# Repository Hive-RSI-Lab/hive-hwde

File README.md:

# hive-pcb-flow

The pcb-flow module: KiCad hardware design for the Hive, in the Hive org like the other modules. It began as ihsan-sa/pcb-flow's Claude Code skill and is its own now ([where it came from](docs/upstream.md)).

An agent designs a PCB from a written brief: research, architecture, parts, schematic, placement, routing, then the checks (ERC, DRC, the verify suite, JLCPCB DFM on the exported Gerbers), ending in a fab package. The person signs off between stages. Ordering and paying are always the person's.

**Where to file issues:** https://github.com/Hive-RSI-Lab/hive-hwde/issues, for a bug or for something that doesn't work on your machine (an Arm computer, another OS): say what you ran and what you saw. An agent in a Hive can draft the issue for you with `hive-report upstream draft`; you read it and press Send.

- [`docs/README.md`](docs/README.md): how an agent uses it in the Hive; [`docs/playbook.md`](docs/playbook.md): the phases, gates and fix loop
- `agents/`: the role prompts the playbook spawns; `scripts/`: the checks and tools; `reference/`: their tables, recipes, checklists and knowledge records
- `tests/`: unit tests for the scripts (`test_env_lookups.py`: the lookups for the Hive's shared tools folder), and `tests/workarounds/`, the probes
- `bin/pcb-flow`: runs the scripts in a Hive sandbox with the Hive's KiCad 10 and freerouting (`pcb-flow check` first)
- The first board made with it: [boards/hwde-led-test/](boards/hwde-led-test/)
- [docs/errata-corpus.md](docs/errata-corpus.md): public boards whose rev B fixed a rev A defect, and which of those defects pcb-flow's checks catch on rev A (`bin/pcb-flow errata_corpus fetch|run|table`)
- [docs/research/](docs/research/README.md): current research turned into checks: `bin/pcb-flow papers` scans the topics in `reference/research/watch.yaml`, reads legitimate open copies (the rest go on [the person's list](docs/research/paywalled.md)), and gives each claim pcb-flow's own verdict, with the test that reached it; only reproduced claims become [guidelines](docs/research/guidelines.md)
- [docs/route-quality.md](docs/route-quality.md): a layout judged as good, not only legal: `route_quality` scores each net class against its shortest 45-degree routes, `route_improve` re-routes the worst nets in rounds and stops when a round stops gaining

## Test and score

- **Test**, `bin/pcb-flow test`, run on every change: upstream's unit tests
  for the skill's scripts (in `tests/`, from ihsan-sa/pcb-flow, about 2,400 of
  them) and the workaround probes. It leaves out tests marked `smoke` (a
  live KiCad run) or `net` (the internet), and points `HWDE_BOARDS_ROOT` at
  an empty dir, so tests that want a real board skip. Upstream tests that
  fail here for a cause a brief already owns are expected failures, listed
  with that brief in `tests/conftest.py`; one that starts passing shows as
  XPASS, and its line comes out. `tests/test_workarounds.py` runs every
  probe in `tests/workarounds/` and fails when
  [docs/workarounds.md](docs/workarounds.md) doesn't match them: a cause
  that stands with no row, or a row whose cause is fixed. It also leaves
  out the tests listed as `slow` in `tests/conftest.py` (`SLOW`: the live
  toolchain, whole fixture boards through bench or the gates, intake of a
  whole project); `bin/pcb-flow test-slow` runs those, so run it too on a change
  to the checks, bench, intake or `check_env`. `bin/pcb-flow test-em` runs the long
  full-wave solves test-slow leaves out (`EM` in `tests/conftest.py`, 80 min
  against test-slow's 17 on a machine at load 45), so run it on a change to `scripts/lib/em*`
  or `scripts/lib/solvers.py`. A test past its limit (15 min, 45 in `em`) fails
  by name. `bin/pcb-flow test-smoke` runs the
  `smoke` tests, whole flows on a live KiCad; CI runs them on every PR and
  daily (`.github/workflows/smoke.yml`), and a failed daily run opens an issue. The test keeps its scratch
  files on `/dev/shm` when it has room and nothing in it fsyncs
  (`HWDE_NO_FSYNC`), because on a loaded disk the suite's file writes, not
  its CPU, set its time; it prints its time and its slowest 15 tests at
  the end. A few minutes; pytest arguments pass through
  (`bin/pcb-flow test tests/test_fab.py -x`).
- **Boards**, `bin/pcb-flow check-all`, not the per-change test: copies every
  board under `boards/` to a scratch dir and re-runs its gate steps there
  through `bin/pcb-flow`: `erc`, `drc_routed`, `verify`, `fab` (gerbers, drill,
  BOM and CPL from `fab_export` and `bom_cpl`) and `dfm`. A board runs each
  gate its `state.json` records as passed, and `fab` once it has a package
  in `fab/`. Any step that fails fails it, and it runs the probes too. Its
  time grows with every board, so run it on a change to the gates, the
  shims in `bin/pcb-flow` or a board, and before a release. Both need
  `/hive/tools`'s KiCad and the Hive's uv; on a fresh HOME they build the
  venv first. Inside a Hive turn both, and the scripts that run a whole
  board, the router or a sim (`route_auto`, `route_critical`,
  `place_anneal`, `gate`, `verify_all`, `bench`, `render`, `sim_run`,
  `sim_solve`, `fab_export`), run under `hive agent heavy`: they wait (at most 10
  minutes) while the machine is strained and other turns run one. A command
  already inside one (check-all's gates, a test that runs `bin/pcb-flow`), or a
  Hive without that op yet, runs bare (`tests/test_heavy.py`).
- **Score**, `bin/pcb-flow score`, higher is better: what this checkout's
  gates get wrong on boards held fixed. The hi-fi receiver's lite-main, core and ultra-front,
  pinned in `pinned/` at one hifi-receiver-2 commit, and hwde-led-test go
  through erc, drc_routed, verify and dfm with `bin/pcb-flow`'s shims off. Each board's
  ledger (`pinned/known/<board>.json`) judges its findings: one held real
  is the board's defect and costs nothing; one held false, one not judged
  yet, a known real one no gate reports any more, and each board-local
  script that stands in for pcb-flow is a charge, and the score is minus the
  charges. A fix in pcb-flow that clears a false finding on those boards raises
  it with nothing written by hand; a sharper check's new real findings go
  into the ledger in the same change. A pinned board changes only through `bin/pcb-flow pin`. The whole
  definition is [docs/score.md](docs/score.md). About ten minutes or more,
  under `hive agent heavy`. A looser check finds less, so the score also
  runs pcb-flow's planted faults (`bin/strength.py`: the gate criteria, every
  verify check's mutant in `tests/golden/`, dfm at JLC's floors), and each
  one a check lets through charges 100.

MIT, like upstream; see NOTICE for what that doesn't cover.

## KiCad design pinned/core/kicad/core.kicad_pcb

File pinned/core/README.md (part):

# core: the Plus/Ultra main board

The main board of hifi-receiver-2's **Plus** and **Ultra** tiers
([docs/product.md](../../docs/product.md)). It is a USB-C-powered
streaming amplifier on one 4-layer board, 154.4 x 113 mm (120 x 100 until the
banana sockets; see below):

- **Input:** 28 V USB PD EPR at up to 140 W.
- **Streaming:** ESP32 with Wi-Fi, Bluetooth and Ethernet.
- **Mains DAC:** Sabre ES9018K2M.
- **Subwoofers:** a separate sub DAC for two sub outputs.
- **Line in:** RCA, with a zero-latency "DJ direct" path.
- **Amp:** two TPA3220 class-D amps (the pad-down TPA3221): 2 x 77 W into 4 ohm peak, no heatsink. Plus plays L on zone A and R on zone B; Ultra drives two pairs.
- **Ultra population options:** a second amp (zone B), an optical input
  and the FFC to the `ultra-front` display board.

It was designed with the hive-hwde module (KiCad 10, JLCPCB) on 2026-10-28,
from schematic through routed layout to a JLC fab package. **Nothing has
been ordered. Ordering is the person's.**

## Status (2026-10-29)

All hwde gates pass on the routed board after the first-spin review ECO, with hive-hwde at c23e27e:

| Gate | Result |
|---|---|
| `erc` | 0 errors, 0 warnings |
| `place` | pass |
| `drc_routed` | 0 errors, 0 warnings, parity clean |
| `verify` | pass, 1 waiver (`reports/verify-waivers.json`: the ESP32 module's 3V3 decoupling loop) |
| `dfm` | pass on the exported Gerbers |

The fab package is in `fab/`:

- **Gerbers:** `core_gerbers.zip`.
- **Plus build:** `BOM.csv` (88 lines, every one with an LCSC number), `CPL.csv` (298 placed parts, 14 of them on the bottom: see `fab/ORDERING.md`), `BOM-full.csv` and `prebuy.csv`, which lists the Extended parts.
- **Ultra build:** `fab/ultra/` holds `BOM.csv` and `CPL.csv` (302 placed parts) for the same Gerbers.

Board facts:

- **Size:** 4 layers, 154.4 x 113 mm overall, 1.6 mm. The right-hand 34.4 mm
  is a wing along the rear only (y < 150 in KiCad); the front right stays
  notched so the ESP32's antenna is still at the board edge.
- **Stackup:** 4 layers, 1.6 mm, 1 oz outer and 1 oz inner. JLC04161H-1080B
  comes only with 0.5 oz inner, so leave Specify Stackup at no requirement
  on the quote page: JLC then builds a 0.203 mm 7628 prepreg and a 1.03 mm
  core, and a named 1 oz layup adds $51.20. No net here is impedance
  controlled. Order it with
  epoxy filled and capped vias (`fab/ORDERING.md`), and inner copper 1 oz, not JLC's 0.5 oz default: the In2 VBUS/PVDD planes carry
  the full 5 A on their own (`power_trunk.py`).
- **Vias:** 0.7/0.3 mm, plus a few 0.45/0.2 mm GND taps.
- **Mounting:** 4 x M3 plated holes.
- **Holes:** JLC's 0.5 mm hole-to-hole spacing is held everywhere.

hwde's own estimate for 10 boards with assembly is $278, $27.84 each. That
excludes the parts, and it is a lower bound: the PCB line has the
oversize-area bug that hive-hwde issue #12 fixes. JLC's cart is the real quote.

## What's on it

The full block list, the ESP32 GPIO map, the I/O expander map, the FFC
pinout and the power tree are in
[architecture/blocks.md](architecture/blocks.md). In short:

| Block | Parts |
|---|---|
| Power in | GCT USB4085-GF-A through-hole USB-C (48 V/5 A, 240 W), CH224Q PD sink (asks for 28 V; ESP32 can read it or change it over I2C), SMBJ30A TVS, 10 mΩ shunt + INA186 current sense |
| PVDD switch | AO4485 P-FET, on only when firmware sets PVDD_EN **and** the CH224Q's PG says the contract is good; ~60 ms soft start (0.47 A, 9.8 W peak); gross-overvoltage cut-off |
| Rails | SY8303 VBUS to 5.1 V; SY8089 5 V to 3.3 V; LP5907 3.3 V analog; ferrite-fed +5VA and +3V3E |
| Processor | ESP32-WROVER-E-N8R8; CH340B USB-serial on the same USB-C (auto-reset, flashing from a laptop) |
| Ethernet | LAN8720A + HR911105A magjack, gated 50 MHz RMII clock |
| Mains DAC | ES9018K2M at 49.152 MHz MCLK, OPA1678 differential-to-single-ended stage |
| Sub DAC | PCM5102A to a stacked dual RCA (SUB1, SUB2) |
| Line in | stacked dual RCA, ES7243E ADC, TS5A23157 DAC/DJ-direct selector |
| Self-measurement | zone A's A_SPK_L+/R+ through 150k/10k, 470 pF, 1 uF onto a 1.65 V bias; TS5A23157 U20 picks RCA input (default) or the taps for the ADC; select from expander P17 through Q7 |
| Zone A amp | TPA3220 (24 dB, AD mode, 600 kHz; pad down, 15 vias into the GND planes), 10 µH / 10 A filters, 4 board-mounted 4 mm banana sockets |
| Zone B amp [Ultra] | the same, synchronised to zone A as a peripheral |
| Control | TCA9539 I/O expander (0x74, reset with the ESP32's EN); Plus front-edge knob, 2 buttons, IR receiver, status LED |
| Optical [Ultra] | PLR237 TOSLINK into the ES9018K2M's S/PDIF mux |
| Front board [Ultra] | 20-pin 0.5 mm FFC to `ultra-front` |

## Plus and Ultra from one board

| Parts | Plus | Ultra |
|---|---|---|
| zone B amp, its filters, bulk cap (U16, L5-L8, C3xx/R3xx) | fitted (plays R) | fitted |
| speaker sockets J20/J21 (zone A L), J26/J27 (zone B R) | fitted | fitted |
| speaker sockets J22/J23 (zone A R), J24/J25 (zone B L) | not fitted | fitted |
| TOSLINK U19, FB3, C126 | not fitted | fitted |
| FFC J3, R402/R403 | not fitted | fitted |
| knob SW1, buttons SW2/SW3, IR U18 (+R400/C400) | fitted | not fitted |

`fab/BOM.csv`/`CPL.csv` are the **Plus** build. `fab/ultra/BOM.csv` and
`CPL.csv` are the **Ultra** build of the same Gerbers.

## Banana sockets (2026-11-01, issues #117, #124)

The speaker outputs are eight 4 mm banana sockets in one row along the rear
edge, 11 mm apart. From the left in KiCad (from behind the box it reads
right to left): J20 A L+, J21 A L-, J22 A R+, J23 A R-, J24 B L+, J25 B L-,
J26 B R+, J27 B R-. Red is +. Plus plays L on zone A and R on zone B
(`HIFI_SPLIT`), so it fits J20/J21 and J26/J27; Ultra fits all eight.

A socket reaches 21.4 mm into the board and its nose stands 2.65 mm past the
edge, so the board grew. The rear edge moved 13 mm back, and a 34.4 mm wing
on the right took the RCA jacks J4/J5 and the TOSLINK U19. They moved with
D7/D8, FB3 and C126 and the copper between them as one block. The mounting
holes H1/H2 went to the new rear corners (H2 later moved south along the east edge to (185.45, 127.4), to make room for the jacks' side ears: `kicad/gen/rca_ear_eco.py`). How it was done, from
`boards/core`, KiCad's python as `python3.11`:

1. `kicad/gen/blocks_amp.py`: the sockets replace the terminals. Then
   `hwde lib_pull --lcsc C7437321 C7437322`, `build.py` (only amp_a/amp_b
   kept), `parts/*.json` by hand, and the netlist.
2. `python3.11 kicad/gen/banana_eco.py kicad/core.kicad_pcb`: rips the old
   terminal copper and the stitch vias under the row, and cuts the speaker
   pours back to y 130. It moves the rear block and the holes, and redraws
   the outline and the planes.
3. `hwde board_update --placements kicad/gen/banana_placements.json`.
4. `python3.11 kicad/gen/banana_route.py kicad/core.kicad_pcb`: one
   staircase pour per speaker net from its old pour to its socket's pin 2.
   L-/R+ run on F.Cu and L+/R- on B.Cu, four per layer, with no crossings
   and no vias. The pours are 2 mm wide (3.7 A rms). Where a later band
   crosses below a socket, its pin 1 joins pin 2 by a 1 mm In2 link (J23,
   J24, J25).
5. `python3.11 kicad/gen/banana_snub.py kicad/core.kicad_pcb`: zone A R- and
   zone B L+'s snubbers reached their net through the old terminal pin. Each
   gets a via and a B.Cu stub into its pour.
6. `miniroute.py` relays SUB1/SUB2_OUT, LIN_L/LIN_R and OPT_SPDIF to the
   moved block. Each line still goes into its ESD clamp (D7/D8) before the
   jack. Stale stubs are ripped with `rip_at.py`, and
   `kicad/gen/banana_silk.py` drops the sockets' silk, as on Lite.
   `kicad/gen/banana_45.py` puts the route ends back on the 45-degree grid
   (hwde check_route_style).

Folded in from review 5: R5-PA-1 (C4 220 nF/50 V C344195, C8 4.7 uF/25 V
C1779: Q1's soft start stays in its SOA), the EP paste windows off the vias
for U9/U10/U13 (`kicad/gen/ep_paste.py`, hwde check_ep_paste), and the
footprints' LCSC fields from parts.json (`kicad/gen/lcsc_fields.py`, run by
`fab.sh`, R5-DAL-8).

## First-spin review (review-2, 2026-10-29)

Six independent reviewers (power, audio, digital/RF, thermal, DFM, parts
pin-to-pad) read this board from its KiCad files and the vendor datasheets:
[`docs/review-2/`](../../docs/review-2/). What changed on core because of it:

| Finding | Was | Now |
|---|---|---|
| DIGITAL-1/2, PARTS-4 (blocker): the TCA9555's pull-ups left PHY_RST (the 50 MHz oscillator into GPIO0, a boot strap), PVDD_EN and the amp/DAC resets mid-rail at power-up, and its outputs held through ESP32 resets | TCA9555, R45 100k | TCA9539 (no pull-ups; RESET = ESP_EN), R45 10k |
| POWER-1 (blocker): the 5 A path ran through 0.25 mm tracks and 1-3 vias | SMD USB4105, few vias | through-hole USB4085 (power pins solid into the In2 VBUS_IN plane), copper patches with 8 vias at R1's input, 10 from R1's output to Q1's source, 8 at Q1's drain; 3-4 per TPA3221 PVDD pin group |
| sim_inrush hard_reset (hwde 261029-050227): Q1's ~1.1 s gate RC outlasted tSrcRecover, so a hard-reset source charged PVDD's 940 uF through a still-on Q1 (14 A, Q1 426 C) | Q2 released, R4 alone pulls the gate | R404 + D5 + Q3's second NPN pull Q1's gate to VBUS in ~2 ms when Q2 lets go (PG lost, PVDD_EN low, OV trip), in hardware: 0.7 A, Q1 120 C in the sim |
| THERMAL-1/DFM-3 (blocker): TPA3221 is pad-up with no heatsink | none | U15/U16 swapped to the pin-identical pad-down TPA3220. Its EP is soldered to GND with 15 x 0.3 mm vias into In1/B.Cu, so nothing is fitted by hand. Plus fits both amps, one channel each (L on zone A, R on zone B), and the firmware governor holds the 60 s average to 19 W out, about 2.0 W per chip, in the vented box (9.6 W/ch into 4 ohm). See `docs/review-2/heatsink-options.md` and `firmware-requirements.md` C2/C3 |
| DFM-1 (blocker): RCA J4/J5 had no holes for the jack's snap-in legs | none | Lite's footprint: 2.0 x 3.0 leg holes, signal pins as slots that fit either reading of the drawing |
| PARTS-7/DFM-12 (blocker, Ultra): TOSLINK T8BK on a T10BK footprint | no post holes | the T8BK's two 1.70 mm post holes (NPTH, `kicad/gen/u19_posts.py`; until 2026-10-30 they were only in the library copy, not on the board) |
| DIGITAL-19 (major): copper under the Wi-Fi antenna on all 4 layers | GND/+3V3 pours, two tracks | `ANT_KEEPOUT` rule area x 148.9-154.64, y 189.6-213.5 on every layer; I2S_DIN and RMII_TXD1 rerouted |
| POWER-2 (major): Q1 turn-on outside its SOA | R4/R5 100k, C8 1 uF | 470k/470k, 2.2 uF/50 V |
| POWER-6 (major): no hardware PVDD cut when the PD contract is lost | Q2 source on GND | Q2 source on CH224Q PG (+ R20 10k pull-up), as on Lite |
| AUDIO-1 (major): OPA1678 at 48 mV of input headroom | R73/75/81/83 1.5k | 1.3k |
| AUDIO-2/3 (major): planned tap switch couldn't pass a node below 0 V or be driven from 3.3 V | (new) | biased tap nodes, Q7 level shift, default = RCA |
| DFM-4 (major): IR receiver looking at the lid | IRM-H638T | front-facing IRM-3638T at the front edge |
| PARTS-3/AUDIO-10, DIGITAL-5, AUDIO-5 (minor) | 50 MHz Y1, C47 100 nF, 1 uF ADC caps | 49.152 MHz, 1 uF, 4.7 uF |
| Stock | CH340C | CH340B |

Ultra's zone-B speaker taps (the bring-up ask) were left out: no control line
is left to choose a zone, and the extra switch crowded the ADC; zone B is
watched through FAULT/OTW and ISENSE. The ES9018K2M's GPIO2 was the first
choice for the tap select, but its pin can't be fanned out between GPIO1 and
DATA, so the select comes from expander P17 and the front board's LCD_CS is
held asserted by R57 (DIGITAL-16; firmware cs = -1).

The changes went in as an ECO on the routed board: `board_update`, the
reviewers' fixes in `kicad/gen/blocks*.py`, then the power patches (then
`via_array.py`, now hwde's `zone_patch`),
`ant_keepout.py`, `miniroute.py`, hwde's `route_auto` (its KRT fallback; Freerouting
stalled), `stitch_vias`, `island_vias.py`/`gnd_via_drops.py` and hand tracks
(`add_track.py`/`add_via.py`). IR_IN keeps a 25 mm hop on In1 (the GND plane)
under the front UI area, where nothing fast crosses it.

## Design decisions and why

These are the decisions that differ from, or add to, docs/product.md.

- **Current sense:** INA186 (40 V), not INA180. The INA180 stops at 26 V
  common mode, under the 28 V rail. The sense taps run through
  10 Ω + 100 nF, but they leave the input planes rather than R1's own pads, so U3 reads
  about 5.6% high (`check_kelvin`, waived in `reports/verify-waivers.json`). It errs on the
  safe side; set the gain at bring-up (`docs/firmware.md`).
- **DAC clock:** 49.152 MHz. With its internal 1.2 V DVDD the
  ES9018K2M is limited to 50 MHz; a 50 MHz part met it only at 0 ppm, so
  review-2 moved to 49.152 MHz (synchronous 1024 x 48 kHz). It covers
  24/96 PCM and 96 kHz S/PDIF.
- **Ethernet clock:** a 50 MHz oscillator drives both the PHY and ESP32
  GPIO0. ESP32 clock-out on GPIO0 is experimental in ESP-IDF. The
  oscillator's enable is the PHY reset line, so GPIO0 boots clean.
- **PVDD switch hold-off:** a gate-source capacitor (1 µF) plus a 15 V
  clamp. Without it, the P-FET turned on while VBUS stepped from 5 to 28 V
  and charged the bulk caps at source slew. A schematic review caught it.
- **Overvoltage cut-off:** a 33 V zener (trips about 32-36 V). It is a
  backstop against gross faults only: the TPA3220's absolute maximum is
  37 V, and a zener cannot trip accurately at 30 V without tripping at the
  legitimate 29.4 V EPR maximum.
- **Snubbers:** on the speaker side of the output filter, as in TI's
  figure 9-1. On the switching node a 1 nF snubber would dissipate 0.47 W
  in each resistor.
- **Speaker outputs:** eight board-mounted 4 mm banana sockets, Amass
  24.243 (red C7437321, black C7437322, 24 A), the part Lite uses. JLC fits
  them, so nothing is wired by hand (issues #117, #124). They replaced 2-way
  5 mm screw terminals, which needed posts in the box wired to them. See
  "Banana sockets" above.
- **Amp polarity:** the TPA3220 inverts. The DAC stage undoes it (U11's
  inputs are swapped), so OUTx_P is the speaker's + (blocks_amp.py).
- **DJ switch logic:** the expander's 3.3 V output can't drive the 5 V
  switch's logic (it needs VIH 3.5 V), so Q6 inverts it up to 5 V.
- **I2S:** one bit and frame clock for all three converters. The sub DAC
  takes its own data pin (I2S1 as slave), because the ESP32 has no pins to
  spare.
- **FFC pinout:** the ultra-front board's map. It needs SPI, I2C and an
  interrupt line, and the front board carries its own expander.
  J3 and ultra-front's J1 are the same socket at rotation 0, pin N on the
  same signal at both ends: the cable is 20-pin 0.5 mm **type B**, pin N to
  pin N (`docs/review-2/resolutions.json` parts:64).

## Rebuild and re-check

From this directory (`boards/core`), with `H="sh $HIVE_MODULES/hive-hwde/bin/hwde"`:

1. **Schematic:**
   `eval "$($H env)"; PYTHONPATH=$HWDE_SKILL/scripts:$HWDE_SKILL/scripts/lib $HWDE_PY kicad/gen/build.py`.
   The design is data in `kicad/gen/blocks*.py`.
2. **ERC:** `$H gate --gate erc kicad/core.kicad_sch --workspace $PWD`
3. **Board setup and placement:** `sh kicad/gen/rebuild_board.sh`. This
   runs board_init, rules_gen, the hand anchors in `kicad/gen/anchors.py`,
   then `kicad/gen/satellites.py` and the place gate.
4. **Routing:** `sh kicad/gen/route.sh` (planes, stitching, Freerouting).
5. **Routed checks and fab:** the `drc_routed`, `verify` and `dfm` gates,
   `fab_export`, and `bom_cpl` run once with `parts/parts.json` (Plus) and
   once with `parts/parts-ultra.json` into `fab/ultra` (Ultra).

The full GND stitching pass (272 vias) went on the routed board afterwards:
[`docs/boards/core-stitch.md`](../../docs/boards/core-stitch.md).

### C43 to the LAN8720A's VDD1A

C43 is the 100 nF on U9 pin 19. It sat 3.8 mm from the pin, but its copper reached the pin only
through 20.3 mm of +3V3E, out through J2.4 and back, so it did little for that pin. ETH_TXN
lies between the two tracks, so `kicad/gen/c43_eco.py` crosses under it on B.Cu with two 0.6/0.3 mm
vias and 1.8 mm of track. The walk is now 6.55 mm, inside hwde's 10 mm limit.

### The two U10 decoupling warnings, left as they are

hwde's `check_decoupling` warns twice on U10 (ES9018K2M). Both are warnings, not errors, and both are left on purpose (2026-11-04):

- **C53 to pin 16 (AVCC_R), 13.7 mm of +3V3A.** Pins 15 (AVCC_L), 16 (AVCC_R) and 17 (VCCA) are joined at the package, 0.5 mm apart.
  So pin 16 is also served by C50 (1 uF, 5.7 mm), C51 (100 nF, 6.1 mm), C54 (100 nF, 7.2 mm) and C52 (1 uF, 7.7 mm), all inside the 10 mm limit.
  C53 is a fifth cap on that group. Its long walk costs nothing the others don't already cover. Moving it would mean new copper beside the DAC outputs for no gain.
- **C55 to pin 18 (DVCC, +3V3), loop about 11.3 nH against a 10 nH limit.** That is 8.8 mm of rail, 3.0 mm of ground and three vias. DVCC is the digital supply that feeds the chip's own 1.2 V regulator, whose output pin 21 (DVDD) has C56 (4.7 uF).
  13 % over the limit moves the cap's self-resonance from about 5.0 to 4.7 MHz. That is not worth a copper change on a board about to be ordered.
  If bring-up shows DAC noise tied to the digital supply, the fix is a 100 nF 0402 placed beside pin 18 on the next spin.

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
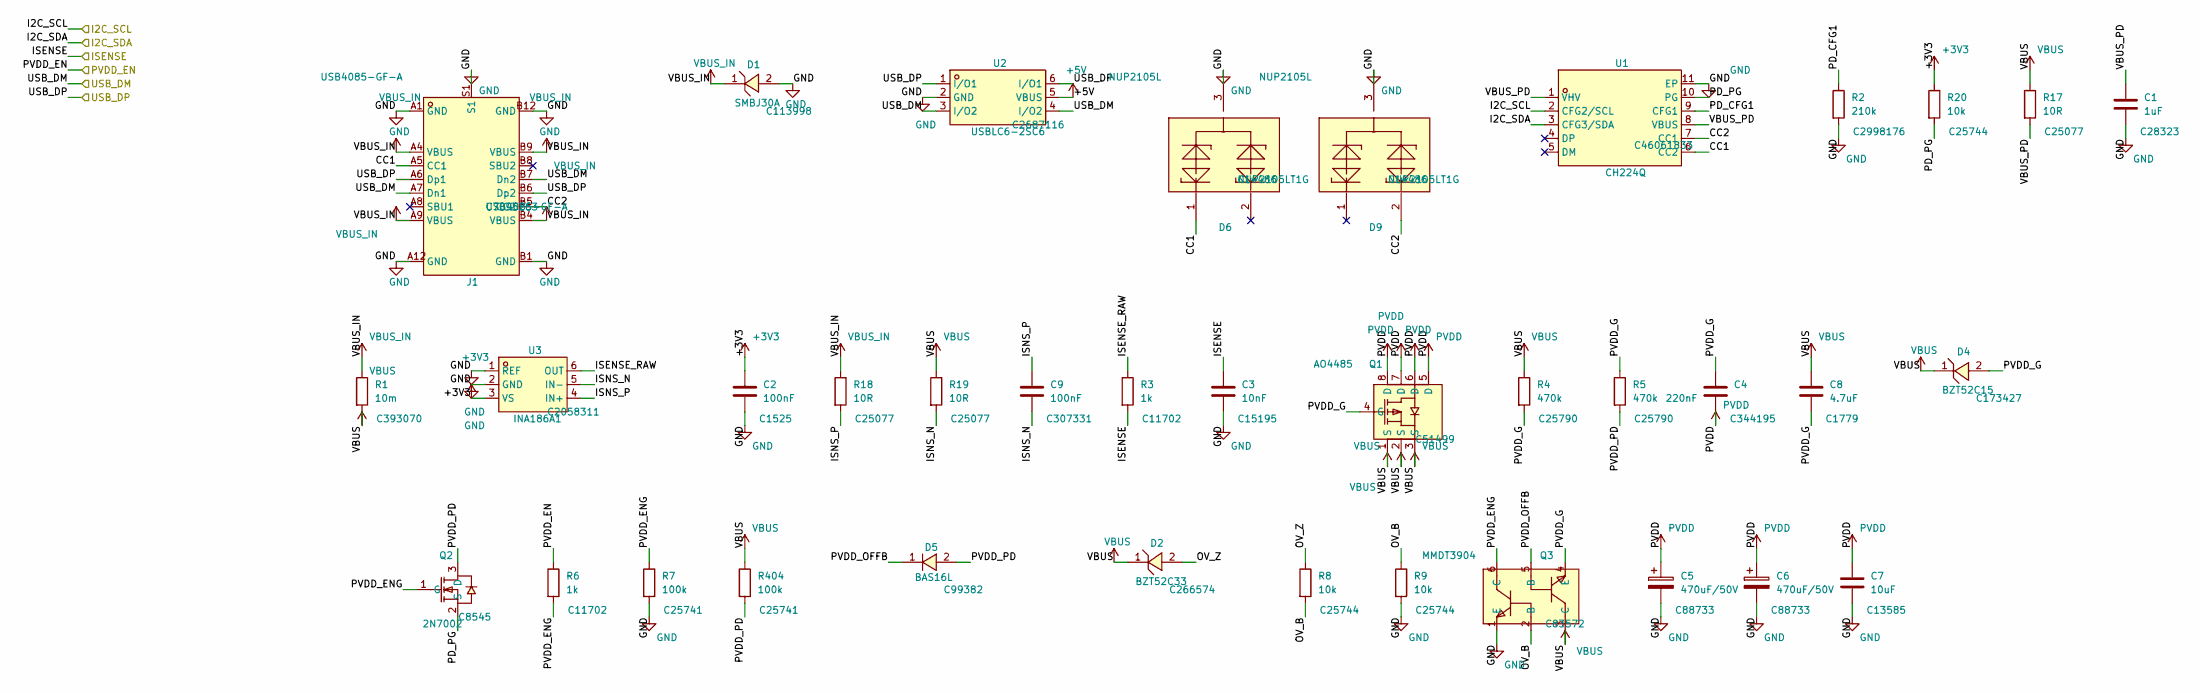
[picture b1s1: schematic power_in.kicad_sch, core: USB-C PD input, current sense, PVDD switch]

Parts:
C1: 1uF; C0805; LCSC C28323
C2: 100nF; C0402; LCSC C1525
C3: 10nF; C0402; LCSC C15195
C4: 220nF; C0603; LCSC C344195
C5, C6: 470uF/50V; CAP-TH_BD10.0-P5.00-D1.0-FD; LCSC C88733
C7: 10uF; C1206; LCSC C13585
C8: 4.7uF; C0805; LCSC C1779
C9: 100nF; C0402; LCSC C307331
D1: SMBJ30A; SMB_L4.6-W3.6-LS5.3-RD; LCSC C113998
D2: BZT52C33; SOD-123_L2.7-W1.6-LS3.7-RD; LCSC C266574
D4: BZT52C15; SOD-123_L2.7-W1.6-LS3.7-RD; LCSC C173427
D5: BAS16L; SOD-882_L1.0-W0.6-RD; LCSC C99382
D6, D9: NUP2105L; SOT-23-3_L2.9-W1.3-P1.90-LS2.4-BL-2; MPN NUP2105LT1G; LCSC C14486
J1: USB4085-GF-A; USC-C-SMD_USB4085-GF-A; MPN USB4085-GF-A; LCSC C7095263
Q1: AO4485; SOIC-8_L5.0-W4.0-P1.27-LS6.0-BL; LCSC C51499
Q2: 2N7002; SOT-23-3_L2.9-W1.3-P1.90-LS2.4-BR; LCSC C8545
Q3: MMDT3904; SOT-363_L2.0-W1.3-P0.65-LS2.1-TL; LCSC C83572
R1: 10m; R2512; LCSC C393070
R2: 210k; R0402; LCSC C2998176
R3, R6: 1k; R0402; LCSC C11702
R4, R5: 470k; R0402; LCSC C25790
R7, R404: 100k; R0402; LCSC C25741
R8, R9, R20: 10k; R0402; LCSC C25744
R17, R18, R19: 10R; R0402; LCSC C25077
U1: CH224Q; DFN-10_L2.0-W2.0-P0.40-BL-EP; LCSC C46061833
U2: USBLC6-2SC6; SOT-23-6_L2.9-W1.6-P0.95-LS2.8-BL; LCSC C2687116
U3: INA186A1; SC-70-6_L2.2-W1.3-P0.65-LS2.1-BR; LCSC C2058311

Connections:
+3V3: C2.1, R20.1, U3.3 (VS); also elsewhere on the board
+5V: U2.5 (VBUS); also elsewhere on the board
/I2C_SCL: U1.2 (CFG2/SCL); also elsewhere on the board
/I2C_SDA: U1.3 (CFG3/SDA); also elsewhere on the board
/ISENSE: C3.1, R3.2; also elsewhere on the board
/PVDD_EN: R6.1; also elsewhere on the board
/USB_DM: J1.A7 (Dn1), J1.B7 (Dn2), U2.3 (I/O2), U2.4 (I/O2); also elsewhere on the board
/USB_DP: J1.A6 (Dp1), J1.B6 (Dp2), U2.1 (I/O1), U2.6 (I/O1); also elsewhere on the board
/power_in/CC1: D6.1, J1.A5 (CC1), U1.6 (CC2)
/power_in/CC2: D9.2, J1.B5 (CC2), U1.7 (CC1)
/power_in/ISENSE_RAW: R3.1, U3.6 (OUT)
/power_in/ISNS_N: C9.2, R19.2, U3.5 (IN-)
/power_in/ISNS_P: C9.1, R18.2, U3.4 (IN+)
/power_in/OV_B: Q3.2 (B), R8.2, R9.1
/power_in/OV_Z: D2.2, R8.1
/power_in/PD_CFG1: R2.1, U1.9 (CFG1)
/power_in/PD_PG: Q2.2 (S), R20.2, U1.10 (PG)
/power_in/PVDD_ENG: Q2.1 (G), Q3.6 (C), R6.2, R7.1
/power_in/PVDD_G: C4.1, C8.2, D4.2 (A), Q1.4 (G), Q3.4 (E), R4.2, R5.1
/power_in/PVDD_OFFB: D5.1 (K), Q3.5 (B)
/power_in/PVDD_PD: D5.2 (A), Q2.3 (D), R5.2, R404.2
/power_in/VBUS_PD: C1.1, R17.2, U1.1 (VHV), U1.8 (VBUS)
GND: C1.2, C2.2, C3.2, C5.2, C6.2, C7.2, D1.2 (A), D6.3, D9.3, J1.A1 (GND), J1.A12 (GND), J1.B1 (GND), J1.B12 (GND), J1.S1, Q3.1 (E), R2.2, R7.2, R9.2, U1.11 (EP), U2.2 (GND), U3.1 (REF), U3.2 (GND); also elsewhere on the board
PVDD: C4.2, C5.1, C6.1, C7.1, Q1.5 (D), Q1.6 (D), Q1.7 (D), Q1.8 (D); also elsewhere on the board
VBUS: C8.1, D2.1, D4.1 (K), Q1.1 (S), Q1.2 (S), Q1.3 (S), Q3.3 (C), R1.2, R4.1, R17.1, R19.1, R404.1; also elsewhere on the board
VBUS_IN: D1.1 (C), J1.A4 (VBUS), J1.A9 (VBUS), J1.B4 (VBUS), J1.B9 (VBUS), R1.1, R18.1

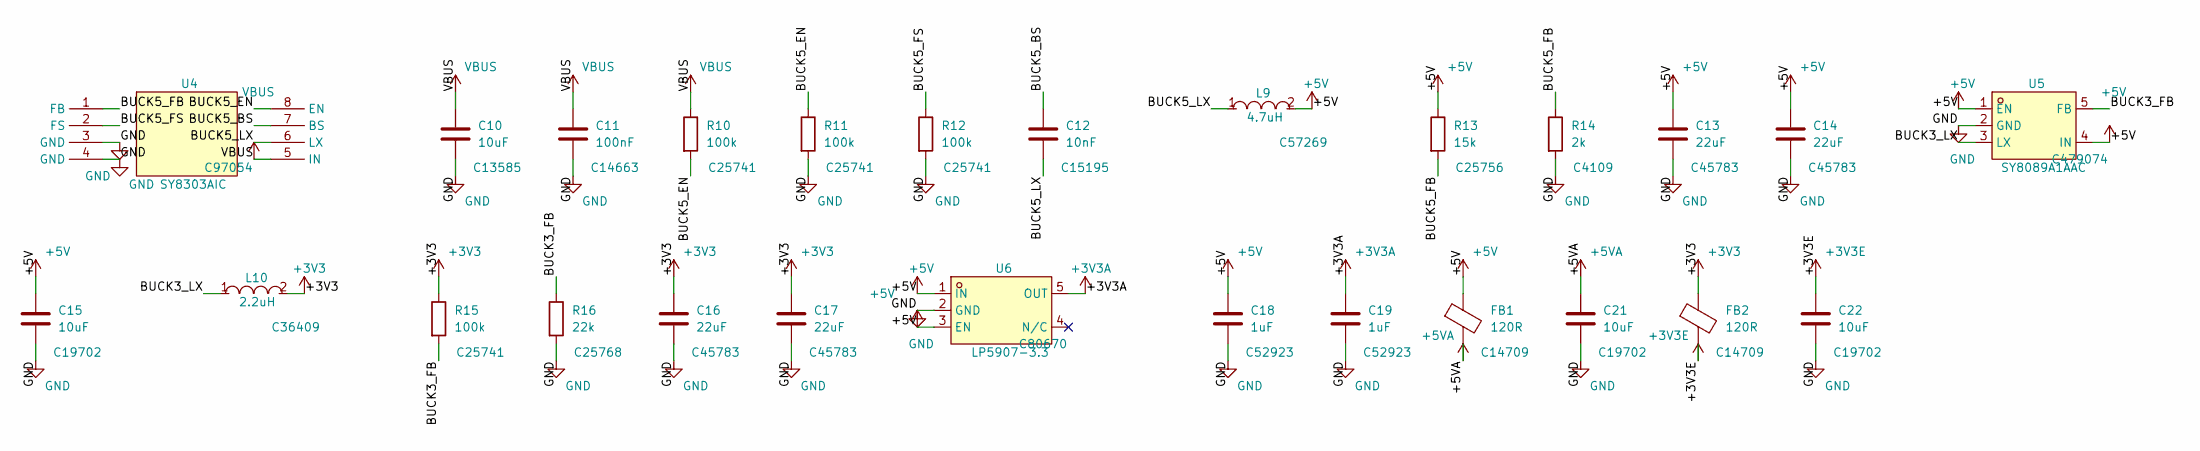
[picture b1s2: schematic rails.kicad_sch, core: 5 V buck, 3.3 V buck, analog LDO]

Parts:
C10: 10uF; C1206; LCSC C13585
C11: 100nF; C0603; LCSC C14663
C12: 10nF; C0402; LCSC C15195
C13, C14, C16, C17: 22uF; C0805; LCSC C45783
C15, C21, C22: 10uF; C0603; LCSC C19702
C18, C19: 1uF; C0402; LCSC C52923
FB1, FB2: 120R; L0603; LCSC C14709
L9: 4.7uH; IND-SMD_L4.0-W4.0; LCSC C57269
L10: 2.2uH; IND-SMD_L4.0-W4.0_LQH44PN2R2MP0L; LCSC C36409
R10, R11, R12, R15: 100k; R0402; LCSC C25741
R13: 15k; R0402; LCSC C25756
R14: 2k; R0402; LCSC C4109
R16: 22k; R0402; LCSC C25768
U4: SY8303AIC; TSOT-23-8_L2.9-W1.6-P0.65-LS2.8-BR; LCSC C97054
U5: SY8089A1AAC; TSOT-23-5_L2.9-W1.6-P0.95-LS2.8-BR; LCSC C479074
U6: LP5907-3.3; SOT-23-5_L3.0-W1.7-P0.95-LS2.8-BR; LCSC C80670

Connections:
+3V3: C16.1, C17.1, FB2.1, L10.2, R15.1; also elsewhere on the board
+3V3A: C19.1, U6.5 (OUT); also elsewhere on the board
+3V3E: C22.1, FB2.2; also elsewhere on the board
+5V: C13.1, C14.1, C15.1, C18.1, FB1.1, L9.2, R13.1, U5.1 (EN), U5.4 (IN), U6.1 (IN), U6.3 (EN); also elsewhere on the board
+5VA: C21.1, FB1.2; also elsewhere on the board
/rails/BUCK3_FB: R15.2, R16.1, U5.5 (FB)
/rails/BUCK3_LX: L10.1, U5.3 (LX)
/rails/BUCK5_BS: C12.1, U4.7 (BS)
/rails/BUCK5_EN: R10.2, R11.1, U4.8 (EN)
/rails/BUCK5_FB: R13.2, R14.1, U4.1 (FB)
/rails/BUCK5_FS: R12.1, U4.2 (FS)
/rails/BUCK5_LX: C12.2, L9.1, U4.6 (LX)
GND: C10.2, C11.2, C13.2, C14.2, C15.2, C16.2, C17.2, C18.2, C19.2, C21.2, C22.2, R11.2, R12.2, R14.2, R16.2, U4.3 (GND), U4.4 (GND), U5.2 (GND), U6.2 (GND); also elsewhere on the board
VBUS: C10.1, C11.1, R10.1, U4.5 (IN); also elsewhere on the board

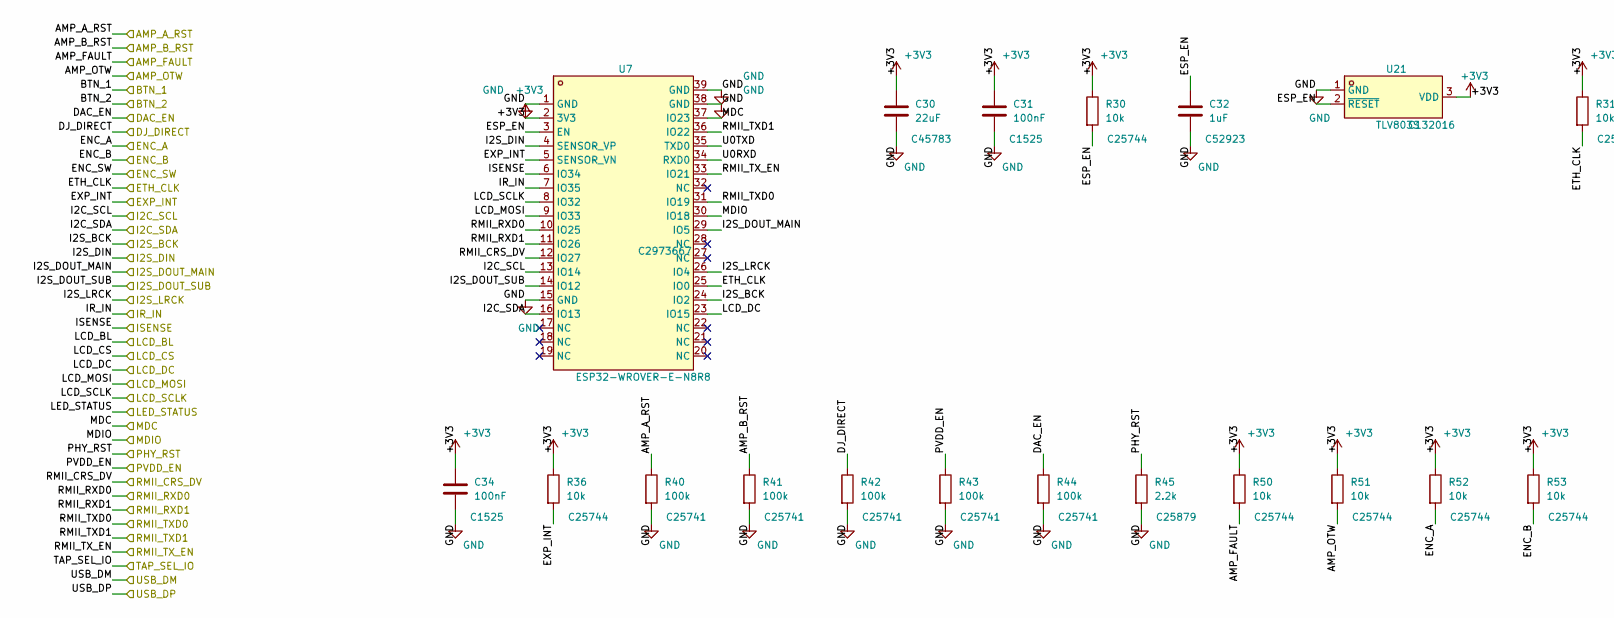
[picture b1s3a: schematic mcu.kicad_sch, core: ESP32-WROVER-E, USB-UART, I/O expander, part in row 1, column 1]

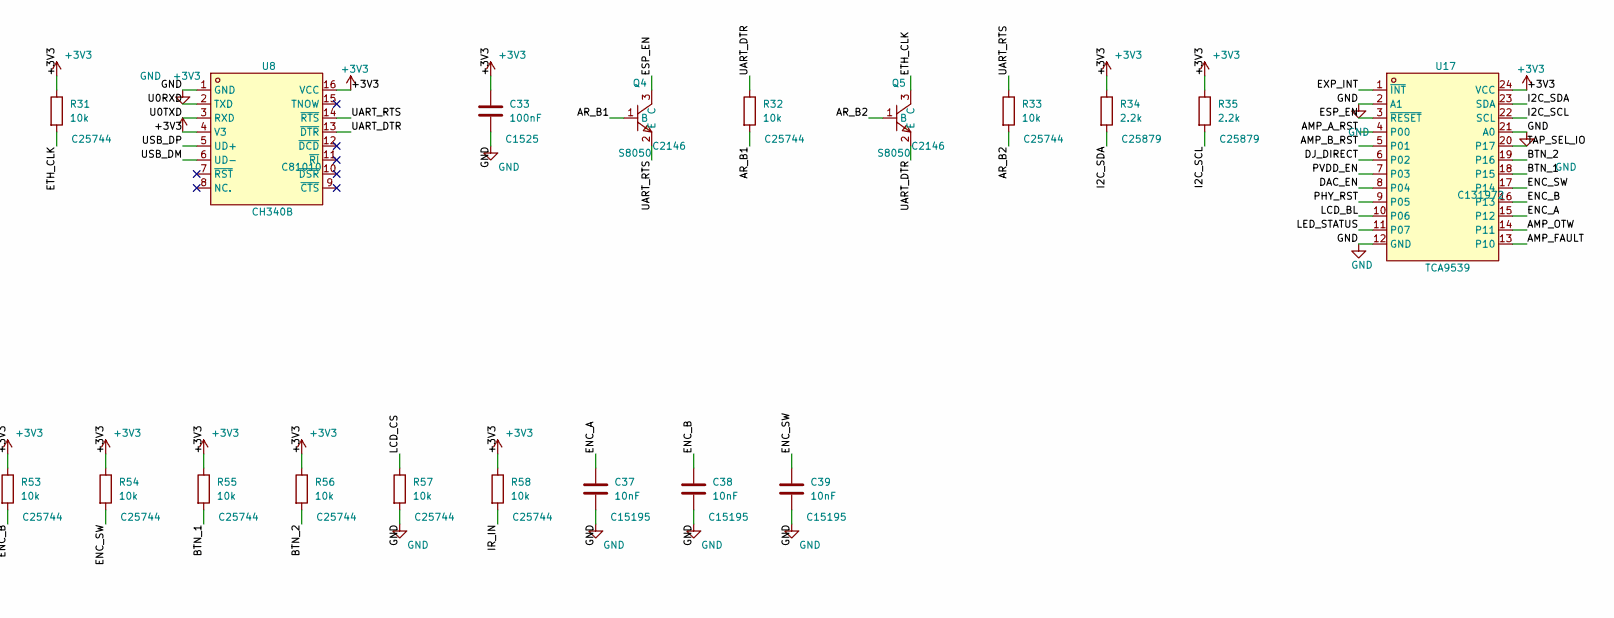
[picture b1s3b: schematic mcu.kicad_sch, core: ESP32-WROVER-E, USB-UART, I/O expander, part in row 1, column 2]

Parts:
C30: 22uF; C0805; LCSC C45783
C31, C33, C34: 100nF; C0402; LCSC C1525
C32: 1uF; C0402; LCSC C52923
C37, C38, C39: 10nF; C0402; LCSC C15195
Q4, Q5: S8050; SOT-23-3_L3.0-W1.7-P0.95-LS2.9-BR; LCSC C2146
R30, R31, R32, R33, R36, R50, R51, R52, R53, R54, R55, R56, R57, R58: 10k; R0402; LCSC C25744
R34, R35, R45: 2.2k; R0402; LCSC C25879
R40, R41, R42, R43, R44: 100k; R0402; LCSC C25741
U7: ESP32-WROVER-E-N8R8; WIFI-SMD_ESP32-WROVER-IE8MB; LCSC C2973667
U8: CH340B; SOP-16_L10.0-W3.9-P1.27-LS6.0-BL; LCSC C81010
U17: TCA9539; TSSOP-24_L7.8-W4.4-P0.65-LS6.4-BL; LCSC C131972
U21: TLV803S; SOT-23-3_L2.9-W1.3-P1.90-LS2.4-BR; LCSC C132016

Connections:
+3V3: C30.1, C31.1, C33.1, C34.1, R30.1, R31.1, R34.1, R35.1, R36.1, R50.1, R51.1, R52.1, R53.1, R54.1, R55.1, R56.1, R58.1, U7.2 (3V3), U8.4 (V3), U8.16 (VCC), U17.24 (VCC), U21.3 (VDD); also elsewhere on the board
/AMP_A_RST: R40.1, U17.4 (P00); also elsewhere on the board
/AMP_B_RST: R41.1, U17.5 (P01); also elsewhere on the board
/AMP_FAULT: R50.2, U17.13 (P10); also elsewhere on the board
/AMP_OTW: R51.2, U17.14 (P11); also elsewhere on the board
/BTN_1: R55.2, U17.18 (P15); also elsewhere on the board
/BTN_2: R56.2, U17.19 (P16); also elsewhere on the board
/DAC_EN: R44.1, U17.8 (P04); also elsewhere on the board
/DJ_DIRECT: R42.1, U17.6 (P02); also elsewhere on the board
/ENC_A: C37.1, R52.2, U17.15 (P12); also elsewhere on the board
/ENC_B: C38.1, R53.2, U17.16 (P13); also elsewhere on the board
/ENC_SW: C39.1, R54.2, U17.17 (P14); also elsewhere on the board
/ETH_CLK: Q5.3 (C), R31.2, U7.25 (IO0); also elsewhere on the board
/EXP_INT: R36.2, U7.5 (SENSOR_VN), U17.1 (~INT); also elsewhere on the board
/I2C_SCL: R35.2, U7.13 (IO14), U17.22 (SCL); also elsewhere on the board
/I2C_SDA: R34.2, U7.16 (IO13), U17.23 (SDA); also elsewhere on the board
/I2S_BCK: U7.24 (IO2); also elsewhere on the board
/I2S_DIN: U7.4 (SENSOR_VP); also elsewhere on the board
/I2S_DOUT_MAIN: U7.29 (IO5); also elsewhere on the board
/I2S_DOUT_SUB: U7.14 (IO12); also elsewhere on the board
/I2S_LRCK: U7.26 (IO4); also elsewhere on the board
/IR_IN: R58.2, U7.7 (IO35); also elsewhere on the board
/ISENSE: U7.6 (IO34); also elsewhere on the board
/LCD_BL: U17.10 (P06); also elsewhere on the board
/LCD_CS: R57.1; also elsewhere on the board
/LCD_DC: U7.23 (IO15); also elsewhere on the board
/LCD_MOSI: U7.9 (IO33); also elsewhere on the board
/LCD_SCLK: U7.8 (IO32); also elsewhere on the board
/LED_STATUS: U17.11 (P07); also elsewhere on the board
/MDC: U7.37 (IO23); also elsewhere on the board
/MDIO: U7.30 (IO18); also elsewhere on the board
/PHY_RST: R45.1, U17.9 (P05); also elsewhere on the board
/PVDD_EN: R43.1, U17.7 (P03); also elsewhere on the board
/RMII_CRS_DV: U7.12 (IO27); also elsewhere on the board
/RMII_RXD0: U7.10 (IO25); also elsewhere on the board
/RMII_RXD1: U7.11 (IO26); also elsewhere on the board
/RMII_TXD0: U7.31 (IO19); also elsewhere on the board
/RMII_TXD1: U7.36 (IO22); also elsewhere on the board
/RMII_TX_EN: U7.33 (IO21); also elsewhere on the board
/TAP_SEL_IO: U17.20 (P17); also elsewhere on the board
/USB_DM: U8.6 (UD-); also elsewhere on the board
/USB_DP: U8.5 (UD+); also elsewhere on the board
/mcu/AR_B1: Q4.1 (B), R32.2
/mcu/AR_B2: Q5.1 (B), R33.2
/mcu/ESP_EN: C32.1, Q4.3 (C), R30.2, U7.3 (EN), U17.3 (~RESET), U21.2 (~RESET)
/mcu/U0RXD: U7.34 (RXD0), U8.2 (TXD)
/mcu/U0TXD: U7.35 (TXD0), U8.3 (RXD)
/mcu/UART_DTR: Q5.2 (E), R32.1, U8.13 (~DTR)
/mcu/UART_RTS: Q4.2 (E), R33.1, U8.14 (~RTS)
GND: C30.2, C31.2, C32.2, C33.2, C34.2, C37.2, C38.2, C39.2, R40.2, R41.2, R42.2, R43.2, R44.2, R45.2, R57.2, U7.1 (GND), U7.15 (GND), U7.38 (GND), U7.39 (GND), U8.1 (GND), U17.2 (A1), U17.12 (GND), U17.21 (A0), U21.1 (GND); also elsewhere on the board

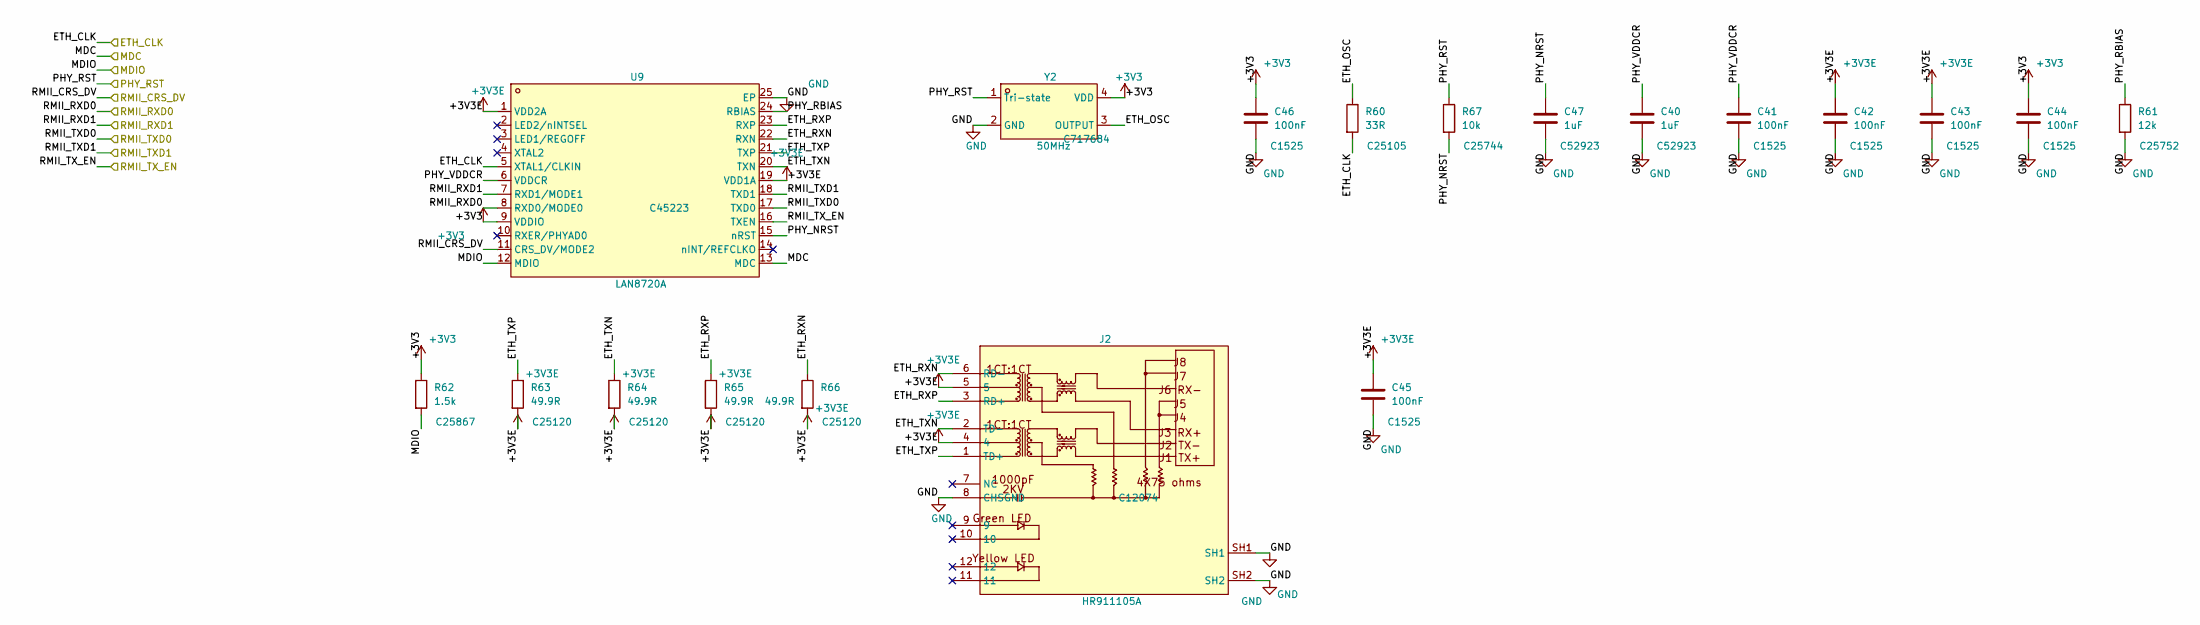
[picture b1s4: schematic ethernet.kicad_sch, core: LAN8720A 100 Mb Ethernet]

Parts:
C40, C47: 1uF; C0402; LCSC C52923
C41, C42, C43, C44, C45, C46: 100nF; C0402; LCSC C1525
J2: HR911105A; RJ45-TH_HR911105A; LCSC C12074
R60: 33R; R0402; LCSC C25105
R61: 12k; R0402; LCSC C25752
R62: 1.5k; R0402; LCSC C25867
R63, R64, R65, R66: 49.9R; R0402; LCSC C25120
R67: 10k; R0402; LCSC C25744
U9: LAN8720A; QFN-24_L4.0-W4.0-P0.50-BL-EP2.6; LCSC C45223
Y2: 50MHz; OSC-SMD_4P-L3.2-W2.5-BL; LCSC C717684

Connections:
+3V3: C44.1, C46.1, R62.1, U9.9 (VDDIO), Y2.4 (VDD); also elsewhere on the board
+3V3E: C42.1, C43.1, C45.1, J2.4, J2.5, R63.2, R64.2, R65.2, R66.2, U9.1 (VDD2A), U9.19 (VDD1A); also elsewhere on the board
/ETH_CLK: R60.2, U9.5 (XTAL1/CLKIN); also elsewhere on the board
/MDC: U9.13 (MDC); also elsewhere on the board
/MDIO: R62.2, U9.12 (MDIO); also elsewhere on the board
/PHY_RST: R67.1, Y2.1 (Tri-state); also elsewhere on the board
/RMII_CRS_DV: U9.11 (CRS_DV/MODE2); also elsewhere on the board
/RMII_RXD0: U9.8 (RXD0/MODE0); also elsewhere on the board
/RMII_RXD1: U9.7 (RXD1/MODE1); also elsewhere on the board
/RMII_TXD0: U9.17 (TXD0); also elsewhere on the board
/RMII_TXD1: U9.18 (TXD1); also elsewhere on the board
/RMII_TX_EN: U9.16 (TXEN); also elsewhere on the board
/ethernet/ETH_OSC: R60.1, Y2.3 (OUTPUT)
/ethernet/ETH_RXN: J2.6 (RD-), R66.1, U9.22 (RXN)
/ethernet/ETH_RXP: J2.3 (RD+), R65.1, U9.23 (RXP)
/ethernet/ETH_TXN: J2.2 (TD-), R64.1, U9.20 (TXN)
/ethernet/ETH_TXP: J2.1 (TD+), R63.1, U9.21 (TXP)
/ethernet/PHY_NRST: C47.1, R67.2, U9.15 (nRST)
/ethernet/PHY_RBIAS: R61.1, U9.24 (RBIAS)
/ethernet/PHY_VDDCR: C40.1, C41.1, U9.6 (VDDCR)
GND: C40.2, C41.2, C42.2, C43.2, C44.2, C45.2, C46.2, C47.2, J2.8 (CHSGND), J2.SH1, J2.SH2, R61.2, U9.25 (EP), Y2.2 (GND); also elsewhere on the board

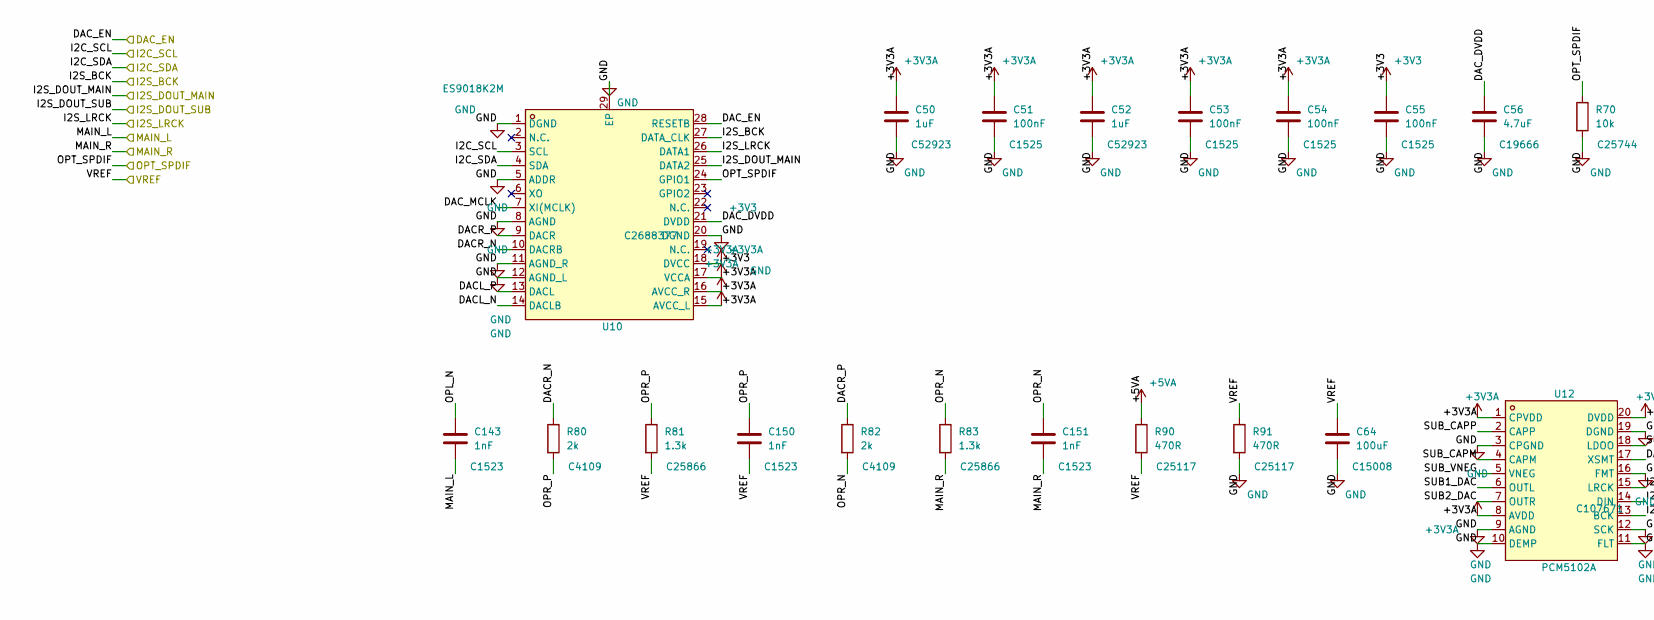
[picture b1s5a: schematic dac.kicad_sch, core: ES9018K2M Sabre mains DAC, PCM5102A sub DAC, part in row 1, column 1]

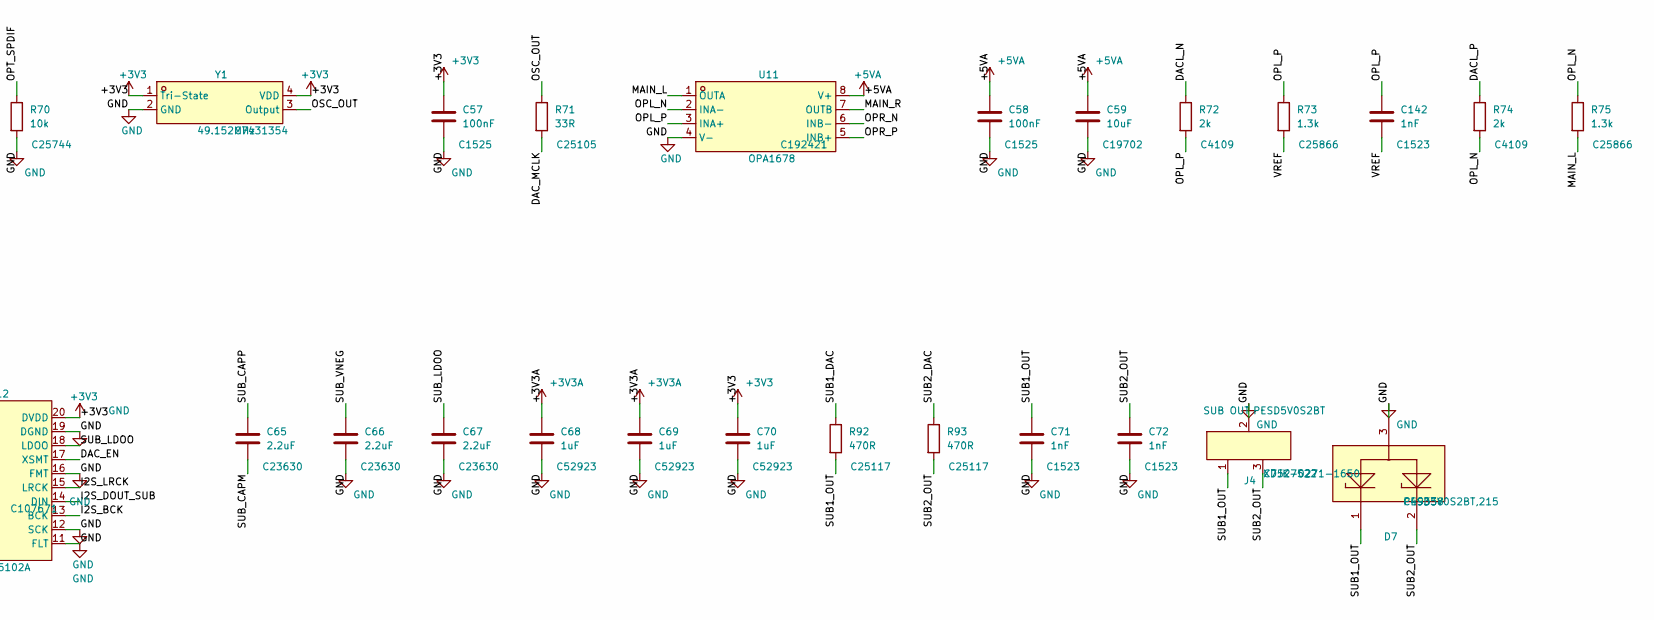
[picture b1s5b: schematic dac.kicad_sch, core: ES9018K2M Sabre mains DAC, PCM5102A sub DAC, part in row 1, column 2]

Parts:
C50, C52, C68, C69, C70: 1uF; C0402; LCSC C52923
C51, C53, C54, C55, C57, C58: 100nF; C0402; LCSC C1525
C56: 4.7uF; C0603; LCSC C19666
C59: 10uF; C0603; LCSC C19702
C64: 100uF; C1206; LCSC C15008
C65, C66, C67: 2.2uF; C0603; LCSC C23630
C71, C72, C142, C143, C150, C151: 1nF; C0402; LCSC C1523
D7: PESD5V0S2BT; SOT-23_L2.9-W1.3-P1.90-LS2.4-BR; MPN PESD5V0S2BT,215; LCSC C49338
J4: SUB OUT; CONN-TH_XDJK-0271-1650; MPN XDJK-0271-1650; LCSC C7527522
R70: 10k; R0402; LCSC C25744
R71: 33R; R0402; LCSC C25105
R72, R74, R80, R82: 2k; R0402; LCSC C4109
R73, R75, R81, R83: 1.3k; R0402; LCSC C25866
R90, R91, R92, R93: 470R; R0402; LCSC C25117
U10: ES9018K2M; QFN-28_L5.0-W5.0-P0.50-BL-EP3.3; LCSC C2688377
U11: OPA1678; SOIC-8_L5.0-W4.0-P1.27-LS6.0-BL; LCSC C192421
U12: PCM5102A; TSSOP-20_L6.5-W4.4-P0.65-LS6.4-BL; LCSC C107671
Y1: 49.152MHz; OSC-SMD_4P-L3.2-W2.5-BL; LCSC C7431354

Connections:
+3V3: C55.1, C57.1, C70.1, U10.18 (DVCC), U12.20 (DVDD), Y1.1 (Tri-State), Y1.4 (VDD); also elsewhere on the board
+3V3A: C50.1, C51.1, C52.1, C53.1, C54.1, C68.1, C69.1, U10.15 (AVCC_L), U10.16 (AVCC_R), U10.17 (VCCA), U12.1 (CPVDD), U12.8 (AVDD); also elsewhere on the board
+5VA: C58.1, C59.1, R90.1, U11.8 (V+); also elsewhere on the board
/DAC_EN: U10.28 (RESETB), U12.17 (XSMT); also elsewhere on the board
/I2C_SCL: U10.3 (SCL); also elsewhere on the board
/I2C_SDA: U10.4 (SDA); also elsewhere on the board
/I2S_BCK: U10.27 (DATA_CLK), U12.13 (BCK); also elsewhere on the board
/I2S_DOUT_MAIN: U10.25 (DATA2); also elsewhere on the board
/I2S_DOUT_SUB: U12.14 (DIN); also elsewhere on the board
/I2S_LRCK: U10.26 (DATA1), U12.15 (LRCK); also elsewhere on the board
/MAIN_L: C143.2, R75.2, U11.1 (OUTA); also elsewhere on the board
/MAIN_R: C151.2, R83.2, U11.7 (OUTB); also elsewhere on the board
/OPT_SPDIF: R70.1, U10.24 (GPIO1); also elsewhere on the board
/VREF: C64.1, C142.2, C150.2, R73.2, R81.2, R90.2, R91.1; also elsewhere on the board
/dac/DACL_N: R72.1, U10.14 (DACLB)
/dac/DACL_P: R74.1, U10.13 (DACL)
/dac/DACR_N: R80.1, U10.10 (DACRB)
/dac/DACR_P: R82.1, U10.9 (DACR)
/dac/DAC_DVDD: C56.1, U10.21 (DVDD)
/dac/DAC_MCLK: R71.2, U10.7 (XI(MCLK))
/dac/OPL_N: C143.1, R74.2, R75.1, U11.2 (INA-)
/dac/OPL_P: C142.1, R72.2, R73.1, U11.3 (INA+)
/dac/OPR_N: C151.1, R82.2, R83.1, U11.6 (INB-)
/dac/OPR_P: C150.1, R80.2, R81.1, U11.5 (INB+)
/dac/OSC_OUT: R71.1, Y1.3 (Output)
/dac/SUB1_DAC: R92.1, U12.6 (OUTL)
/dac/SUB1_OUT: C71.1, D7.1, J4.1, R92.2
/dac/SUB2_DAC: R93.1, U12.7 (OUTR)
/dac/SUB2_OUT: C72.1, D7.2, J4.3, R93.2
/dac/SUB_CAPM: C65.2, U12.4 (CAPM)
/dac/SUB_CAPP: C65.1, U12.2 (CAPP)
/dac/SUB_LDOO: C67.1, U12.18 (LDOO)
/dac/SUB_VNEG: C66.1, U12.5 (VNEG)
GND: C50.2, C51.2, C52.2, C53.2, C54.2, C55.2, C56.2, C57.2, C58.2, C59.2, C64.2, C66.2, C67.2, C68.2, C69.2, C70.2, C71.2, C72.2, D7.3, J4.2, R70.2, R91.2, U10.1 (DGND), U10.5 (ADDR), U10.8 (AGND), U10.11 (AGND_R), U10.12 (AGND_L), U10.20 (DGND), U10.29 (EP), U11.4 (V-), U12.3 (CPGND), U12.9 (AGND), U12.10 (DEMP), U12.11 (FLT), U12.12 (SCK), U12.16 (FMT), U12.19 (DGND), Y1.2 (GND); also elsewhere on the board
